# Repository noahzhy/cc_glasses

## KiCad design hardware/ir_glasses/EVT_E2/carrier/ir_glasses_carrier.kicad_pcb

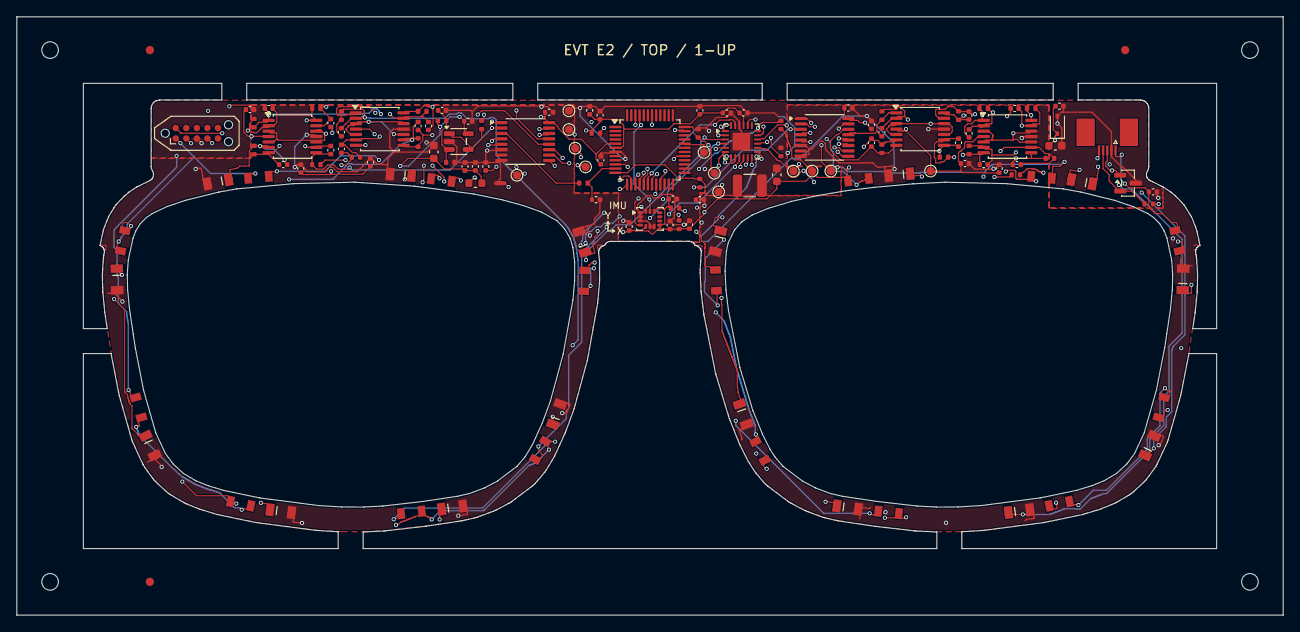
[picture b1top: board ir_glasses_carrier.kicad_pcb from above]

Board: 4 copper layers, 152.3 x 72.0 mm, 143 parts (0 on the bottom side), 79 nets.

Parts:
C1, C18, C19, C20, C21, C22, C23, C24: 1u; C_0402_1005Metric
C2, C3, C4, C5, C6, C7, C8, C9, C10, C11, C12, C13, C14, C15, C16, C17, C31: 100n; C_0402_1005Metric
C25, C26, C27: 10u; C_0603_1608Metric
C28: 47u 16V X5R; C_1210_3225Metric
C29, C30: 1n; C_0402_1005Metric
CF1, CF2, CF3, CF4, CF5, CF6, CF7, CF8, CF9, CF10, CF11, CF12, CF13, CF14, CF15, CF16: 22p C0G; C_0402_1005Metric
D1, D2, D3, D4, D5, D6, D7, D8, D9, D10, D11, D12, D13, D14, D15, D16: IR11-21C/TR8; Everlight_IR11_21C
D17: PESD5V0S1BA,115; D_SOD-323
FB1: 600R@100MHz 500mA; L_0603_1608Metric
FID1, FID2, FID3: Fiducial_1mm_Mask2mm
H1, H2, H3, H4: MountingHole_2mm
J1: 2492111-5; TE_2492111-5_1x05_P0.5mm_Horizontal
J2: TC2050-IDC-NL / ARM2010; Tag-Connect_TC2050-IDC-NL_2x05_P1.27mm_Vertical
NT1: AGND-GND star; NetTie-2_SMD_Pad0.5mm
PD1, PD2, PD3, PD4, PD5, PD6, PD7, PD8, PD9, PD10, PD11, PD12, PD13, PD14, PD15, PD16: PD15-21B/TR8; Everlight_PD15_21B
R1: 2.67k; R_0402_1005Metric
R2, R3, R4, R10: 10k; R_0402_1005Metric
R5: 100k; R_0402_1005Metric
R6, R7: 4.7k; R_0402_1005Metric
R8, R9: 22; R_0402_1005Metric
R11, R12: 100; R_0402_1005Metric
R13: 47; R_0402_1005Metric
RF1, RF2, RF3, RF4, RF5, RF6, RF7, RF8, RF9, RF10, RF11, RF12, RF13, RF14, RF15, RF16: 100k; R_0402_1005Metric
TP1, TP10: 3V3; TestPoint_Pad_D1.0mm
TP2: GND; TestPoint_Pad_D1.0mm
TP3: UART_TX; TestPoint_Pad_D1.0mm
TP4: UART_RX; TestPoint_Pad_D1.0mm
TP5: BOOT_TX_PA9; TestPoint_Pad_D1.0mm
TP6: BOOT_RX_PA10; TestPoint_Pad_D1.0mm
TP7: SWCLK_BOOT0; TestPoint_Pad_D1.0mm
TP8: NRST; TestPoint_Pad_D1.0mm
TP9: VREF_1V65; TestPoint_Pad_D1.0mm
TP11: IMU_INT; TestPoint_Pad_D1.0mm
TP12: 3V3_A; TestPoint_Pad_D1.0mm
U1: TLC59283RGER; Texas_RGE0024C_VQFN-24-1EP_4x4mm_P0.5mm_EP2.1x2.1mm
U2, U3, U4, U5: TLV9064IPWR; TSSOP-14_4.4x5mm_P0.65mm
U6: TLV9061IDBVR; SOT-23-5
U7, U8: TMUX1308PWR; TSSOP-16_4.4x5mm_P0.65mm
U9: STM32C031C6T6; LQFP-48_7x7mm_P0.5mm
U10: LSM6DS3TR-C; LGA-14_3x2.5mm_P0.5mm_LayoutBorder3x4y
U11: PESD3V3L2BT,215; SOT-23

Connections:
3V3: C2.1, C10.1, C12.1, C13.1, C14.1, C16.1, C17.1, C18.1, C19.1, C20.1, C24.1, C25.1, C26.1, C28.1, D1.1, D2.1, D3.1, D4.1, D5.1, D6.1, D7.1, D8.1, D9.1, D10.1, D11.1, D12.1, D13.1, D14.1, D15.1, D16.1, D17.1, FB1.1, J1.1, J2.1, R4.1, R6.1, R7.1, R10.1, TP1.1, TP10.1, U1.21, U9.6, U10.5, U10.8, U10.12
3V3_A: C3.1, C4.1, C5.1, C6.1, C7.1, C8.1, C9.1, C11.1, C15.1, C21.1, C22.1, C23.1, C27.1, FB1.2, R2.1, TP12.1, U2.4, U3.4, U4.4, U5.4, U6.5, U7.16, U8.16, U9.5
ADC_L: C29.1, R11.2, U9.11
ADC_R: C30.1, R12.2, U9.12
AGND: C1.2, C3.2, C4.2, C5.2, C6.2, C7.2, C8.2, C9.2, C15.2, C21.2, C22.2, C23.2, C27.2, C29.2, C30.2, C31.2, NT1.1, PD1.1, PD2.1, PD3.1, PD4.1, PD5.1, PD6.1, PD7.1, PD8.1, PD9.1, PD10.1, PD11.1, PD12.1, PD13.1, PD14.1, PD15.1, PD16.1, R3.2, U2.11, U3.11, U4.11, U5.11, U6.2, U7.6, U7.8, U8.6, U8.8
BOOT_RX_PA10: TP6.1, U9.32
BOOT_TX_PA9: TP5.1, U9.29
GND: C2.2, C10.2, C11.2, C12.2, C13.2, C14.2, C16.2, C17.2, C18.2, C19.2, C20.2, C24.2, C25.2, C26.2, C28.2, D17.2, J1.2, J2.3, NT1.2, R1.2, R5.2, TP2.1, U1.22, U1.25, U9.7, U10.1, U10.2, U10.3, U10.6, U10.7, U11.3
HOST_RX: J1.4, R9.1, U11.2
HOST_TX: J1.3, R8.2, U11.1
I2C_SCL: R6.2, U9.45, U10.13
I2C_SDA: R7.2, U9.46, U10.14
IMU_INT: TP11.1, U9.42, U10.4
IREF: R1.1, U1.20
LED_BLANK: R10.2, U1.18, U9.21
LED_K1: D1.2, U1.2
LED_K2: D2.2, U1.3
LED_K3: D3.2, U1.4
LED_K4: D4.2, U1.5
LED_K5: D5.2, U1.6
LED_K6: D6.2, U1.7
LED_K7: D7.2, U1.8
LED_K8: D8.2, U1.9
LED_K9: D9.2, U1.10
LED_K10: D10.2, U1.11
LED_K11: D11.2, U1.12
LED_K12: D12.2, U1.13
LED_K13: D13.2, U1.14
LED_K14: D14.2, U1.15
LED_K15: D15.2, U1.16
LED_K16: D16.2, U1.17
LED_LAT: U1.1, U9.20
LED_SCLK: U1.24, U9.16
LED_SIN: U1.23, U9.18
MUX_A0: U7.11, U8.11, U9.15
MUX_A1: U7.10, U8.10, U9.17
MUX_A2: U7.9, U8.9, U9.19
MUX_L: R11.1, U7.3
MUX_R: R12.1, U8.3
NRST: J1.5, J2.10, R4.2, TP8.1, U9.10
PD_IN1: CF1.2, PD1.2, RF1.2, U2.2
PD_IN2: CF2.2, PD2.2, RF2.2, U2.6
PD_IN3: CF3.2, PD3.2, RF3.2, U2.9
PD_IN4: CF4.2, PD4.2, RF4.2, U2.13
PD_IN5: CF5.2, PD5.2, RF5.2, U3.2
PD_IN6: CF6.2, PD6.2, RF6.2, U3.6
PD_IN7: CF7.2, PD7.2, RF7.2, U3.9
PD_IN8: CF8.2, PD8.2, RF8.2, U3.13
PD_IN9: CF9.2, PD9.2, RF9.2, U4.2
PD_IN10: CF10.2, PD10.2, RF10.2, U4.6
PD_IN11: CF11.2, PD11.2, RF11.2, U4.9
PD_IN12: CF12.2, PD12.2, RF12.2, U4.13
PD_IN13: CF13.2, PD13.2, RF13.2, U5.2
PD_IN14: CF14.2, PD14.2, RF14.2, U5.6
PD_IN15: CF15.2, PD15.2, RF15.2, U5.9
PD_IN16: CF16.2, PD16.2, RF16.2, U5.13
SWCLK_BOOT0: J2.4, R5.1, TP7.1, U9.36
SWDIO: J2.2, U9.35
TIA1: CF1.1, RF1.1, U2.1, U7.13
TIA2: CF2.1, RF2.1, U2.7, U7.14
TIA3: CF3.1, RF3.1, U2.8, U7.15
TIA4: CF4.1, RF4.1, U2.14, U7.12
TIA5: CF5.1, RF5.1, U3.1, U7.1
TIA6: CF6.1, RF6.1, U3.7, U7.5
TIA7: CF7.1, RF7.1, U3.8, U7.2
TIA8: CF8.1, RF8.1, U3.14, U7.4
TIA9: CF9.1, RF9.1, U4.1, U8.13
TIA10: CF10.1, RF10.1, U4.7, U8.14
TIA11: CF11.1, RF11.1, U4.8, U8.15
TIA12: CF12.1, RF12.1, U4.14, U8.12
TIA13: CF13.1, RF13.1, U5.1, U8.1
TIA14: CF14.1, RF14.1, U5.7, U8.5
TIA15: CF15.1, RF15.1, U5.8, U8.2
TIA16: CF16.1, RF16.1, U5.14, U8.4
UART_RX: R9.2, TP4.1, U9.14
UART_TX: R8.1, TP3.1, U9.13
VREF_1V65: C31.1, R13.2, TP9.1, U2.3, U2.5, U2.10, U2.12, U3.3, U3.5, U3.10, U3.12, U4.3, U4.5, U4.10, U4.12, U5.3, U5.5, U5.10, U5.12
VREF_BUF: R13.1, U6.1, U6.4
VREF_DIV: C1.1, R2.2, R3.1, U6.3

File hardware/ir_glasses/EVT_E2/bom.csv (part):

Reference,Value,Footprint,Quantity,Populate,X_mm,Y_mm,Rotation_deg,Side,Manufacturer,MPN,LCSC
U9,STM32C031C6T6,IR_Glasses:LQFP-48_7x7mm_P0.5mm,1,Yes,110.0,63.0,0.0,front,STMicroelectronics,STM32C031C6T6,C5456218
U1,TLC59283RGER,IR_Glasses:Texas_RGE0024C_VQFN-24-1EP_4x4mm_P0.5mm_EP2.1x2.1mm,1,Yes,121.0,62.0,0.0,front,Texas Instruments,TLC59283RGER,C485815
U10,LSM6DS3TR-C,IR_Glasses:LGA-14_3x2.5mm_P0.5mm_LayoutBorder3x4y,1,Yes,110.0,71.3,0.0,front,STMicroelectronics,LSM6DS3TR-C,C967633
U6,TLV9061IDBVR,IR_Glasses:SOT-23-5,1,Yes,87.0,62.0,0.0,front,Texas Instruments,TLV9061IDBVR,C398358
J1,2492111-5,IR_Glasses:TE_2492111-5_1x05_P0.5mm_Horizontal,1,Yes,165.0,61.7,180.0,front,TE Connectivity,2492111-5,
J2,TC2050-IDC-NL / ARM2010,IR_Glasses:Tag-Connect_TC2050-IDC-NL_2x05_P1.27mm_Vertical,1,PCB pads only,55.5,61.0,0.0,front,,,
U11,"PESD3V3L2BT,215",IR_Glasses:SOT-23,1,Yes,167.5,67.0,0.0,front,Nexperia,"PESD3V3L2BT,215",C55440
D17,"PESD5V0S1BA,115",IR_Glasses:D_SOD-323,1,Yes,159.0,60.0,90.0,front,Nexperia,"PESD5V0S1BA,115",C19224
FB1,600R@100MHz 500mA,IR_Glasses:L_0603_1608Metric,1,Yes,89.0,67.0,0.0,front,Murata,BLM18AG601SN1D,C19330
NT1,AGND-GND star,IR_Glasses:NetTie-2_SMD_Pad0.5mm,1,PCB pads only,92.0,67.0,0.0,front,,,
R1,2.67k,IR_Glasses:R_0402_1005Metric,1,Yes,125.75,63.25,90.0,front,Viking,ARG02FTC2671,C284464
R2,10k,IR_Glasses:R_0402_1005Metric,1,Yes,85.0,59.5,0.0,front,UNI-ROYAL,0402WGF1002TCE,C25744
R3,10k,IR_Glasses:R_0402_1005Metric,1,Yes,86.0,64.5,0.0,front,UNI-ROYAL,0402WGF1002TCE,C25744
R4,10k,IR_Glasses:R_0402_1005Metric,1,Yes,103.5,61.0,0.0,front,UNI-ROYAL,0402WGF1002TCE,C25744
R5,100k,IR_Glasses:R_0402_1005Metric,1,Yes,115.8,61.0,90.0,front,UNI-ROYAL,0402WGF1003TCE,C25741
R6,4.7k,IR_Glasses:R_0402_1005Metric,1,Yes,113.0,70.0,0.0,front,UNI-ROYAL,0402WGF4701TCE,C25900
R7,4.7k,IR_Glasses:R_0402_1005Metric,1,Yes,113.5,72.0,90.0,front,UNI-ROYAL,0402WGF4701TCE,C25900
R8,22,IR_Glasses:R_0402_1005Metric,1,Yes,154.0,66.0,0.0,front,UNI-ROYAL,0402WGF220JTCE,C25092
R9,22,IR_Glasses:R_0402_1005Metric,1,Yes,170.0,69.5,0.0,front,UNI-ROYAL,0402WGF220JTCE,C25092
R10,10k,IR_Glasses:R_0402_1005Metric,1,Yes,125.75,60.0,90.0,front,UNI-ROYAL,0402WGF1002TCE,C25744
R11,100,IR_Glasses:R_0402_1005Metric,1,Yes,102.0,67.0,0.0,front,UNI-ROYAL,0402WGF1000TCE,C25076
R12,100,IR_Glasses:R_0402_1005Metric,1,Yes,116.0,67.0,90.0,front,UNI-ROYAL,0402WGF1000TCE,C25076
R13,47,IR_Glasses:R_0402_1005Metric,1,Yes,89.75,60.0,90.0,front,UNI-ROYAL,0402WGF470JTCE,C25118
U2,TLV9064IPWR,IR_Glasses:TSSOP-14_4.4x5mm_P0.65mm,1,Yes,77.5,60.5,0.0,front,Texas Instruments,TLV9064IPWR,C779410
U3,TLV9064IPWR,IR_Glasses:TSSOP-14_4.4x5mm_P0.65mm,1,Yes,67.0,61.4,0.0,front,Texas Instruments,TLV9064IPWR,C779410
PD1,PD15-21B/TR8,IR_Glasses:Everlight_PD15_21B,1,Yes,98.7722,94.7937,69.734,front,Everlight,PD15-21B/TR8,C2921391
D1,IR11-21C/TR8,IR_Glasses:Everlight_IR11_21C,1,Yes,96.7988,99.1302,60.632,front,Everlight,IR11-21C/TR8,C16745
RF1,100k,IR_Glasses:R_0402_1005Metric,1,Yes,72.888,58.875,90.0,front,UNI-ROYAL,0402WGF1003TCE,C25741
CF1,22p C0G,IR_Glasses:C_0402_1005Metric,1,Yes,72.888,60.875,90.0,front,FH,0402CG220J500NT,C1555
PD2,PD15-21B/TR8,IR_Glasses:Everlight_PD15_21B,1,Yes,86.2325,106.021,8.481,front,Everlight,PD15-21B/TR8,C2921391
D2,IR11-21C/TR8,IR_Glasses:Everlight_IR11_21C,1,Yes,81.3078,106.6029,6.53,front,Everlight,IR11-21C/TR8,C16745
RF2,100k,IR_Glasses:R_0402_1005Metric,1,Yes,74.638,63.875,0.0,front,UNI-ROYAL,0402WGF1003TCE,C25741
CF2,22p C0G,IR_Glasses:C_0402_1005Metric,1,Yes,72.888,62.875,90.0,front,FH,0402CG220J500NT,C1555
PD3,PD15-21B/TR8,IR_Glasses:Everlight_PD15_21B,1,Yes,65.5918,106.4508,-7.387,front,Everlight,PD15-21B/TR8,C2921391
D3,IR11-21C/TR8,IR_Glasses:Everlight_IR11_21C,1,Yes,60.7691,105.5578,-11.779,front,Everlight,IR11-21C/TR8,C16745
RF3,100k,IR_Glasses:R_0402_1005Metric,1,Yes,82.112,62.125,90.0,front,UNI-ROYAL,0402WGF1003TCE,C25741
CF3,22p C0G,IR_Glasses:C_0402_1005Metric,1,Yes,82.112,60.125,90.0,front,FH,0402CG220J500NT,C1555
PD4,PD15-21B/TR8,IR_Glasses:Everlight_PD15_21B,1,Yes,49.8952,98.5678,-64.946,front,Everlight,PD15-21B/TR8,C2921391
D4,IR11-21C/TR8,IR_Glasses:Everlight_IR11_21C,1,Yes,48.4901,93.9754,-74.093,front,Everlight,IR11-21C/TR8,C16745
RF4,100k,IR_Glasses:R_0402_1005Metric,1,Yes,82.612,58.375,0.0,front,UNI-ROYAL,0402WGF1003TCE,C25741
CF4,22p C0G,IR_Glasses:C_0402_1005Metric,1,Yes,83.362,60.125,90.0,front,FH,0402CG220J500NT,C1555
PD5,PD15-21B/TR8,IR_Glasses:Everlight_PD15_21B,1,Yes,45.894,78.5794,-88.524,front,Everlight,PD15-21B/TR8,C2921391
D5,IR11-21C/TR8,IR_Glasses:Everlight_IR11_21C,1,Yes,46.5765,73.926999,-102.15,front,Everlight,IR11-21C/TR8,C16745
RF5,100k,IR_Glasses:R_0402_1005Metric,1,Yes,62.388,59.775,90.0,front,UNI-ROYAL,0402WGF1003TCE,C25741
CF5,22p C0G,IR_Glasses:C_0402_1005Metric,1,Yes,64.138,58.025,0.0,front,FH,0402CG220J500NT,C1555
PD6,PD15-21B/TR8,IR_Glasses:Everlight_PD15_21B,1,Yes,58.0382,66.8263,-168.75,front,Everlight,PD15-21B/TR8,C2921391
D6,IR11-21C/TR8,IR_Glasses:Everlight_IR11_21C,1,Yes,62.9055,66.2981,-174.743,front,Everlight,IR11-21C/TR8,C16745
RF6,100k,IR_Glasses:R_0402_1005Metric,1,Yes,62.388,63.025,90.0,front,UNI-ROYAL,0402WGF1003TCE,C25741
CF6,22p C0G,IR_Glasses:C_0402_1005Metric,1,Yes,65.888,64.775,0.0,front,FH,0402CG220J500NT,C1555
PD7,PD15-21B/TR8,IR_Glasses:Everlight_PD15_21B,1,Yes,80.031,66.001599,176.212,front,Everlight,PD15-21B/TR8,C2921391
D7,IR11-21C/TR8,IR_Glasses:Everlight_IR11_21C,1,Yes,84.912,66.631599,172.509,front,Everlight,IR11-21C/TR8,C16745
RF7,100k,IR_Glasses:R_0402_1005Metric,1,Yes,69.862,64.775,0.0,front,UNI-ROYAL,0402WGF1003TCE,C25741
CF7,22p C0G,IR_Glasses:C_0402_1005Metric,1,Yes,71.612,63.025,90.0,front,FH,0402CG220J500NT,C1555
PD8,PD15-21B/TR8,IR_Glasses:Everlight_PD15_21B,1,Yes,101.8327,74.0665,106.613,front,Everlight,PD15-21B/TR8,C2921391
D8,IR11-21C/TR8,IR_Glasses:Everlight_IR11_21C,1,Yes,102.0915,78.7534,87.41,front,Everlight,IR11-21C/TR8,C16745
RF8,100k,IR_Glasses:R_0402_1005Metric,1,Yes,69.862,58.025,0.0,front,UNI-ROYAL,0402WGF1003TCE,C25741
CF8,22p C0G,IR_Glasses:C_0402_1005Metric,1,Yes,71.612,59.775,90.0,front,FH,0402CG220J500NT,C1555
U7,TMUX1308PWR,IR_Glasses:TSSOP-16_4.4x5mm_P0.65mm,1,Yes,95.0,62.0,0.0,front,Texas Instruments,TMUX1308PWR,C970231
U4,TLV9064IPWR,IR_Glasses:TSSOP-14_4.4x5mm_P0.65mm,1,Yes,142.5,60.5,0.0,front,Texas Instruments,TLV9064IPWR,C779410
U5,TLV9064IPWR,IR_Glasses:TSSOP-14_4.4x5mm_P0.65mm,1,Yes,153.0,61.4,0.0,front,Texas Instruments,TLV9064IPWR,C779410
PD9,PD15-21B/TR8,IR_Glasses:Everlight_PD15_21B,1,Yes,121.206099,94.7917,-70.355,front,Everlight,PD15-21B/TR8,C2921391
D9,IR11-21C/TR8,IR_Glasses:Everlight_IR11_21C,1,Yes,123.253199,99.2161,-63.186,front,Everlight,IR11-21C/TR8,C16745
RF9,100k,IR_Glasses:R_0402_1005Metric,1,Yes,137.888,58.875,90.0,front,UNI-ROYAL,0402WGF1003TCE,C25741
CF9,22p C0G,IR_Glasses:C_0402_1005Metric,1,Yes,137.888,60.875,90.0,front,FH,0402CG220J500NT,C1555
PD10,PD15-21B/TR8,IR_Glasses:Everlight_PD15_21B,1,Yes,133.767499,106.021,-8.481,front,Everlight,PD15-21B/TR8,C2921391
D10,IR11-21C/TR8,IR_Glasses:Everlight_IR11_21C,1,Yes,138.6922,106.6029,-6.53,front,Everlight,IR11-21C/TR8,C16745
RF10,100k,IR_Glasses:R_0402_1005Metric,1,Yes,137.888,62.875,90.0,front,UNI-ROYAL,0402WGF1003TCE,C25741
CF10,22p C0G,IR_Glasses:C_0402_1005Metric,1,Yes,136.638,62.125,90.0,front,FH,0402CG220J500NT,C1555
PD11,PD15-21B/TR8,IR_Glasses:Everlight_PD15_21B,1,Yes,154.4082,106.4508,7.387,front,Everlight,PD15-21B/TR8,C2921391
D11,IR11-21C/TR8,IR_Glasses:Everlight_IR11_21C,1,Yes,159.2309,105.5578,11.779,front,Everlight,IR11-21C/TR8,C16745
RF11,100k,IR_Glasses:R_0402_1005Metric,1,Yes,145.362,63.875,0.0,front,UNI-ROYAL,0402WGF1003TCE,C25741
CF11,22p C0G,IR_Glasses:C_0402_1005Metric,1,Yes,147.112,62.125,90.0,front,FH,0402CG220J500NT,C1555
PD12,PD15-21B/TR8,IR_Glasses:Everlight_PD15_21B,1,Yes,170.1048,98.5678,64.946,front,Everlight,PD15-21B/TR8,C2921391
D12,IR11-21C/TR8,IR_Glasses:Everlight_IR11_21C,1,Yes,171.5099,93.9754,74.093,front,Everlight,IR11-21C/TR8,C16745
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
